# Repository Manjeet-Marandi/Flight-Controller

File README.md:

# Flight-Controller
This repository contains the KiCad design files for a custom flight controller PCB designed for multirotor drones.  
The board integrates multiple sensors and communication interfaces into a compact layout.

## Features

- STM32F746VGT7 microcontroller
- USB
- SD
- Flash
- IMU (Inertial Measurement Unit)
- GPS module interface
- Barometer
- Telemetry and RC input/output
- Voltage regulators
- Expansion headers for peripherals

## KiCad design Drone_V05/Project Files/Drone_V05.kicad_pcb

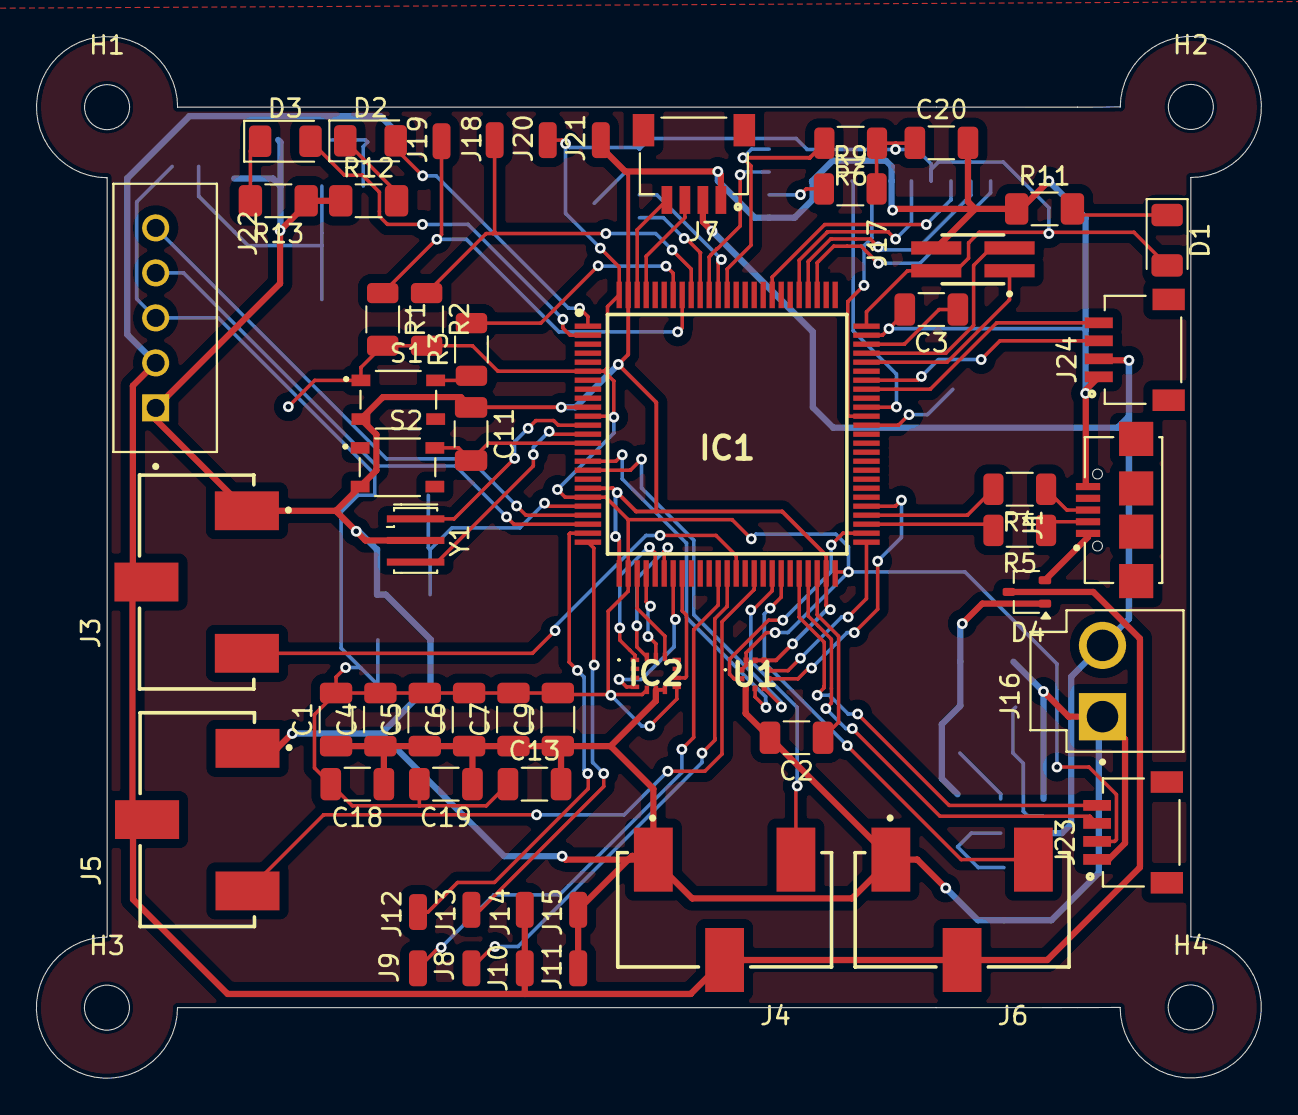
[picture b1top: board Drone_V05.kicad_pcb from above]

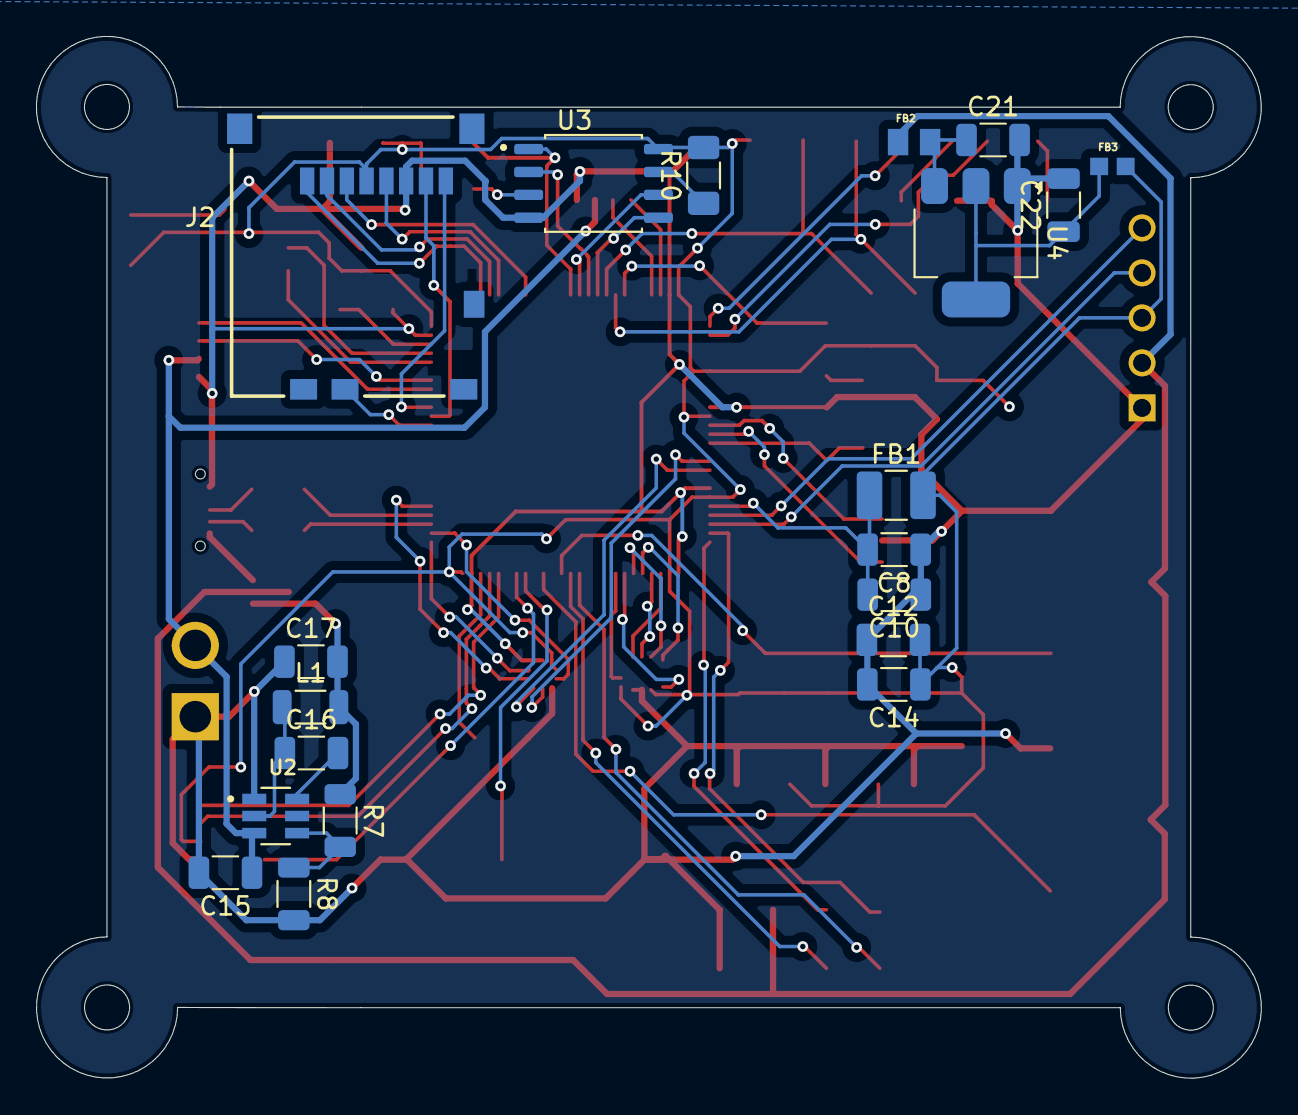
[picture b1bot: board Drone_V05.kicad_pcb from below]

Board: 2 copper layers, 68.0 x 57.9 mm, 80 parts (20 on the bottom side), 72 nets.

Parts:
C1, C15, C21, C22: 10u; C_1206_3216Metric
C2, C3: 2.2u; C_1206_3216Metric
C4, C5, C6, C7, C9, C11, C20: 0.1u; C_1206_3216Metric
C8: 10n; C_1206_3216Metric
C10, C12: 1u; C_1206_3216Metric
C13, C14, C16, C18, C19: 100n; C_1206_3216Metric
C17: 44u; C_1206_3216Metric
D1, D2, D3: LED; LED_1206_3216Metric
D4: BAT54CW; SOT-323_SC-70
FB1: 120MHz; L_1210_3225Metric_Pad1.42x2.65mm_HandSolder
FB2: 100MHz; BEADC2012X105N
FB3: 100MHz; BEADC1608X95N
H1, H2, H3, H4: MountingHole; MountingHole_2.5mm
IC1: STM32F746VGT7; QFP50P1600X1600X160-100N
IC2: BMI323
J1: UJ2-MIBH-G-SMT-TR; CUI_UJ2-MIBH-G-SMT-TR
J2: 5025700893; MOLEX_5025700893
J3, J4, J5, J6: HFWJ-03-X-X-S-VS; SAMTEC_HFWJ-03-X-X-S-VS
J7, J23, J24: SM04B-SRSS-TB_LF__SN_; JST_SM04B-SRSS-TB_LF__SN_
J8, J9, J10, J11, J12, J13, J14, J15, J18, J19, J20, J21: Conn_01x01_Pin; SolderWirePad_1x01_SMD_1x2mm
J16: B2P-VH_LF__SN_; JST_B2P-VH_LF__SN_
J17: FTSH-102-01-G-DV; SAMTEC_FTSH-102-01-G-DV
J22: B5B-XH-A_LF__SN_; JST_B5B-XH-A_LF__SN_
L1: 3.3u; L_1206_3216Metric
R1, R2: 2k; R_1206_3216Metric
R3, R6, R8, R9: 10k; R_1206_3216Metric
R4, R5: 22; R_1206_3216Metric
R7: 52.3k; R_1206_3216Metric
R10: 10k; R_1206_3216Metric_Pad1.30x1.75mm_HandSolder
R11, R12, R13: 500; R_1206_3216Metric_Pad1.30x1.75mm_HandSolder
S1, S2: SKRPACE010; SW_SKRPACE010
U1: BMP581
U2: AP62301WU-7; SOT95P280X100-6N
U3: W25Q16JVSSIQ; SOIC127P790X216-8N
U4: AMS1117-3.3; SOT-223-3_TabPin2
Y1: 16MHz; Resonator_SMD_Murata_CSTxExxV-3Pin_3.0x1.1mm_HandSoldering

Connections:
+5V: D4.3, FB2.1, J3.02, J4.02, J5.02, J6.02, J10.1, J14.1, J22.2
+5V_REG: C17.2, D4.1, L1.2, R7.1
+5V_USB: D4.2, J1.1 (VCC)
+BATT: C15.1, J7.2, J16.2, J24.2, U2.3 (VIN)
/I2C1_SCL: IC1.92 (PB6), J18.1, R2.1
/I2C1_SDA: IC1.93 (PB7), J19.1, R1.1
BMI_INT1: IC1.32 (PC4), IC2.4 (INT1)
BMI_INT2: IC1.33 (PC5), IC2.9 (INT2)
BMP_CS: IC1.55 (PD8), U1.6 (CSB)
BMP_INT: IC1.51 (PB12), U1.7 (INT)
BOOT: IC1.94 (BOOT0), R3.2
CAM_RX: IC1.97 (PE0), J7.3
CAM_TX: IC1.98 (PE1), J7.4
COMP_RX: IC1.69 (PA10), J24.3
COMP_TX: IC1.68 (PA9), J24.4
ESC1: IC1.39 (PE9), J3.03
ESC2: IC1.41 (PE11), J5.03
ESC3: IC1.43 (PE13), J4.03
ESC4: IC1.44 (PE14), J6.03
FLASH_CLK: IC1.89 (PB3), U3.6 (CLK)
FLASH_CS: IC1.88 (PD7), R6.2, U3.1 (~CS)
GPS_RX: IC1.47 (PB11), J23.3
GPS_TX: IC1.46 (PB10), J23.4
GYRO_CS: IC1.28 (PA4), IC2.12 (CSB)
LED1: D2.2 (A), IC1.1 (PE2)
LED2: D3.2 (A), IC1.2 (PE3)
NRST: C11.2, IC1.14 (NRST), S2.2
unnamed: D1.1 (K), R11.2
unnamed: D2.1 (K), R12.2
unnamed: D3.1 (K), R13.2
unnamed: IC1.12 (PH0-_OSC_IN), Y1.1
unnamed: IC1.13 (PH1-_OSC_OU_T), Y1.3
unnamed: J1.3 (D+), R4.1
unnamed: J1.2 (D-), R5.1
unnamed: R3.1, S1.2
unnamed: C16.2, U2.6 (BST)
unnamed: R7.2, R8.1, U2.4 (FB)
unnamed: C16.1, L1.1, U2.2 (SW)
unnamed: R10.1, U3.7 (~HOLD/RESET(IO3))
unnamed: R9.1, U3.3 (~WP(IO2))
unnamed: C21.1, FB2.2, U4.3 (VI)
unnamed: C22.1, FB3.1, U4.2 (VO)
RF_RX: IC1.25 (PA3), J13.1
RF_TX: IC1.24 (PA2), J12.1
SD_CK: IC1.80 (PC12), J2.5 (CLK)
SD_CMD: IC1.83 (PD2), J2.3 (CMD)
SD_D0: IC1.65 (PC8), J2.7 (DAT0)
SD_D1: IC1.66 (PC9), J2.8 (DAT1)
SD_D2: IC1.78 (PC10), J2.1 (DAT2)
SD_D3: IC1.79 (PC11), J2.2 (DAT3/CD)
SD_DET: IC1.64 (PC7), J2.10 (DET_SW)
SPI1_MISO: IC1.30 (PA6), IC2.1 (SDO)
SPI1_MOSI: IC1.31 (PA7), IC2.14 (SDX)
SPI1_SCK: IC1.29 (PA5), IC2.13 (SCX)
SPI2_MISO: IC1.17 (PC2), U1.5 (SDO)
SPI2_MOSI: IC1.16 (PC1), U1.4 (SDI)
SPI2_SCK: IC1.52 (PB13), U1.2 (SCK)
SPI3_MISO: IC1.90 (PB4), U3.2 (DO(IO1))
SPI3_MOSI: IC1.91 (PB5), U3.5 (DI(IO0))
SWCLK: IC1.71 (PA12), J17.01
SWDIO: IC1.72 (PA13), J17.03
TELE_RX: IC1.37 (PE7), J9.1
TELE_TX: IC1.38 (PE8), J8.1
UART4_RX: IC1.23 (PA1), J22.4
UART4_TX: IC1.22 (PA0-WKUP), J22.5
USB_D+: IC1.54 (PB15), R4.2
USB_D-: IC1.53 (PB14), R5.2
VBAT: C1.2, C4.2, C5.2, C6.2, C7.2, C9.2, C12.2, C13.1, C14.1, C18.2, C19.2, C20.1, D1.2 (A), FB1.2, FB3.2, IC1.6 (VBAT), IC1.11 (VDD_1), IC1.20 (VREF+), IC1.27 (VDD_2), IC1.50 (VDD_3), IC1.75 (VDD_4), IC1.100 (VDD_5), IC2.5 (VDDIO), IC2.8 (VDD), J2.4 (VDD), J17.02, J20.1, J22.3, J23.2, R1.2, R2.2, R6.1, R9.2, R10.2, S1.1, U1.1 (VDDIO), U1.10 (VDD), U3.8 (VCC)
VCAP1: C2.1, IC1.48 (VCAP1)
VCAP2: C3.1, IC1.73 (VCAP2)
VDDA: C8.2, C10.2, FB1.1, IC1.21 (VDDA)
VSS: C1.1, C2.2, C3.2, C4.1, C5.1, C6.1, C7.1, C8.1, C9.1, C10.1, C11.1, C12.1, C13.2, C14.2, C15.2, C17.1, C18.1, C19.1, C20.2, C21.2, C22.2, IC1.10 (VSS_1), IC1.19 (VSSA), IC1.26 (VSS_2), IC1.49 (VSS_3), IC1.74 (VSS_4), IC1.99 (VSS_5), IC2.6 (GNDIO), IC2.7 (GND), J1.5 (GND), J2.6 (VSS), J3.01, J4.01, J5.01, J6.01, J7.1, J11.1, J15.1, J16.1, J17.04, J21.1, J22.1, J23.1, J24.1, R8.2, R11.1, R12.1, R13.1, S1.3, S2.3, U1.3 (VSS_1), U1.8 (VSS_2), U1.9 (VSS_3), U2.1 (GND), U3.4 (GND), U4.1 (GND), Y1.2

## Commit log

2025-07-14 Create Drone_V05
2025-07-14 Create KiCad project files
2025-07-14 Create test
2025-07-14 Create temp
